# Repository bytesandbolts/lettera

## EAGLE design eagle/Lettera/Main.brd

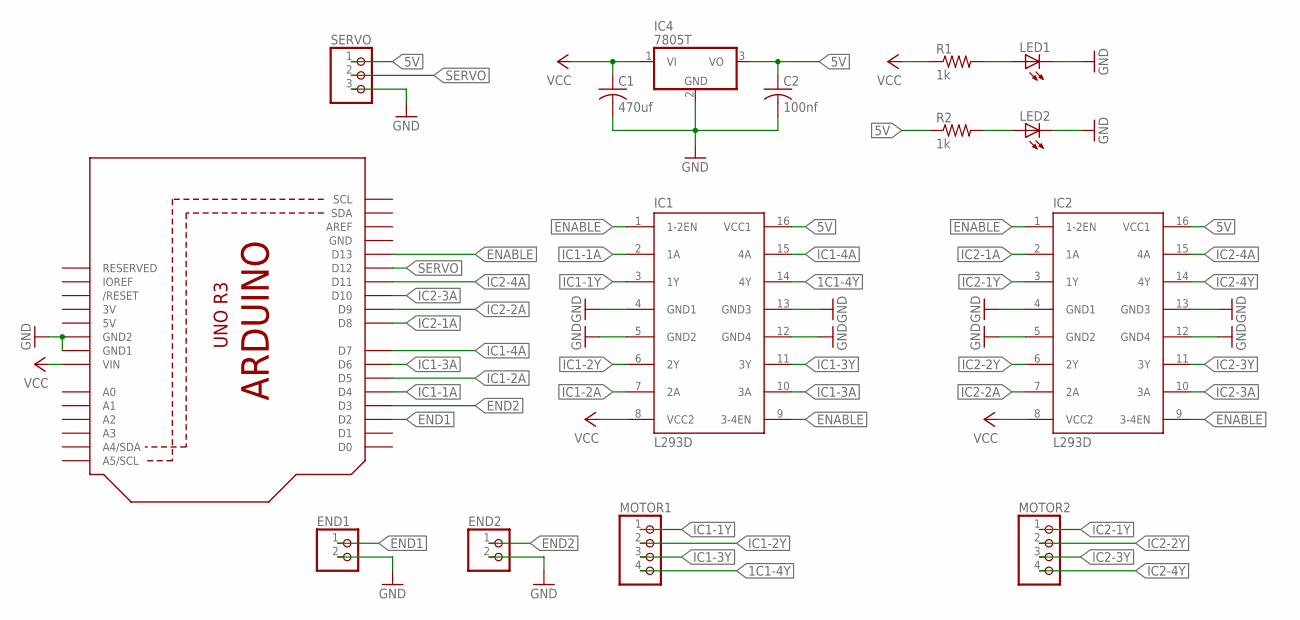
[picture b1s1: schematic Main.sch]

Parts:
C1: 470uf; C025-025X050
C2: 100nf; C025-025X050
END1, END2: PINHD-1X2; 1X02
IC1, IC2: L293D; DIL16
IC4: 7805T; TO220H
LED1, LED2: LED3MM
MOTOR1, MOTOR2: PINHD-1X4; 1X04
R1, R2: 1k; 0204/7
SERVO: PINHD-1X3; 1X03
U1: ARDUINOR3-BPLACE

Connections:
1C1-4Y: IC1.14 (4Y), MOTOR1.4
3V: U1.3V
5V: C2.1, IC1.16 (VCC1), IC2.16 (VCC1), IC4.3 (VO), R2.1, SERVO.1, U1.5V
ENABLE: IC1.1 (1-2EN), IC1.9 (3-4EN), IC2.1 (1-2EN), IC2.9 (3-4EN), U1.D13
END1: END1.1, U1.D2
END2: END2.1, U1.D3
GND: C1.2, C2.2, END1.2, END2.2, IC1.4 (GND1), IC1.5 (GND2), IC1.12 (GND4), IC1.13 (GND3), IC2.4 (GND1), IC2.5 (GND2), IC2.12 (GND4), IC2.13 (GND3), IC4.2 (GND), LED1.K (C), LED2.K (C), SERVO.3, U1.GND, U1.GND1, U1.GND2
IC1-1A: IC1.2 (1A), U1.D4
IC1-1Y: IC1.3 (1Y), MOTOR1.1
IC1-2A: IC1.7 (2A), U1.D5
IC1-2Y: IC1.6 (2Y), MOTOR1.2
IC1-3A: IC1.10 (3A), U1.D6
IC1-3Y: IC1.11 (3Y), MOTOR1.3
IC1-4A: IC1.15 (4A), U1.D7
IC2-1A: IC2.2 (1A), U1.D8
IC2-1Y: IC2.3 (1Y), MOTOR2.1
IC2-2A: IC2.7 (2A), U1.D9
IC2-2Y: IC2.6 (2Y), MOTOR2.2
IC2-3A: IC2.10 (3A), U1.D10
IC2-3Y: IC2.11 (3Y), MOTOR2.3
IC2-4A: IC2.15 (4A), U1.D11
IC2-4Y: IC2.14 (4Y), MOTOR2.4
unnamed: LED1.A, R1.2
unnamed: LED2.A, R2.2
SERVO: SERVO.2, U1.D12
VCC: C1.1, IC1.8 (VCC2), IC2.8 (VCC2), IC4.1 (VI), R1.1, U1.VIN

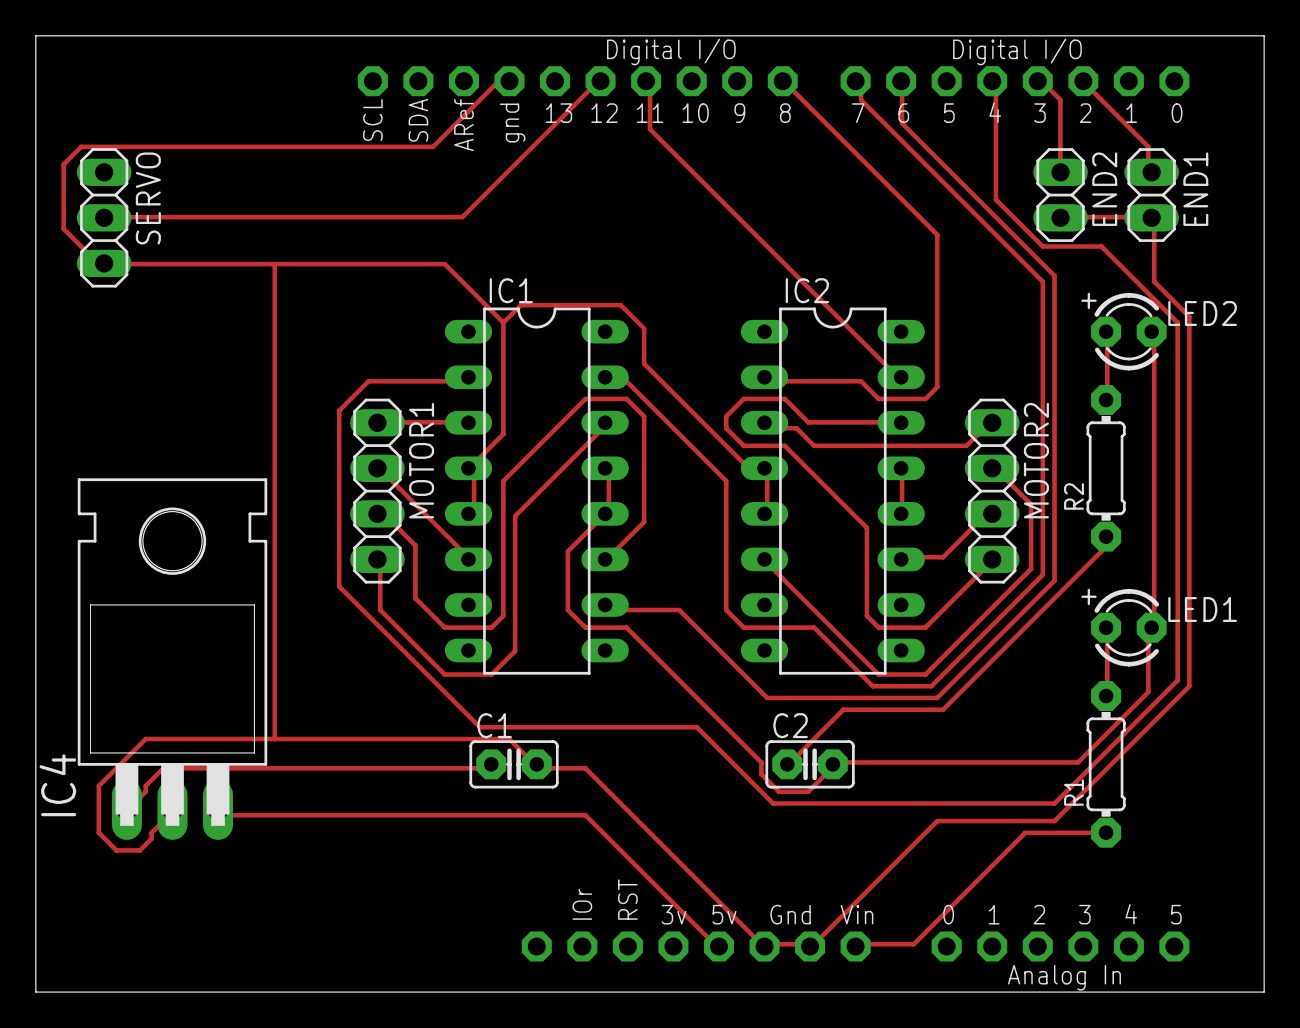
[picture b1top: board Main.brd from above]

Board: 2 copper layers, 68.5 x 53.3 mm, 15 parts (0 on the bottom side), 25 nets.

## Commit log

2016-08-02 Added inital project files
